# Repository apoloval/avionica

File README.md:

## Introduction

Avionica is a electronics platform used to build flight simulation systems.

## Status

Avionica is a work in progress. There is nothing usable yet.

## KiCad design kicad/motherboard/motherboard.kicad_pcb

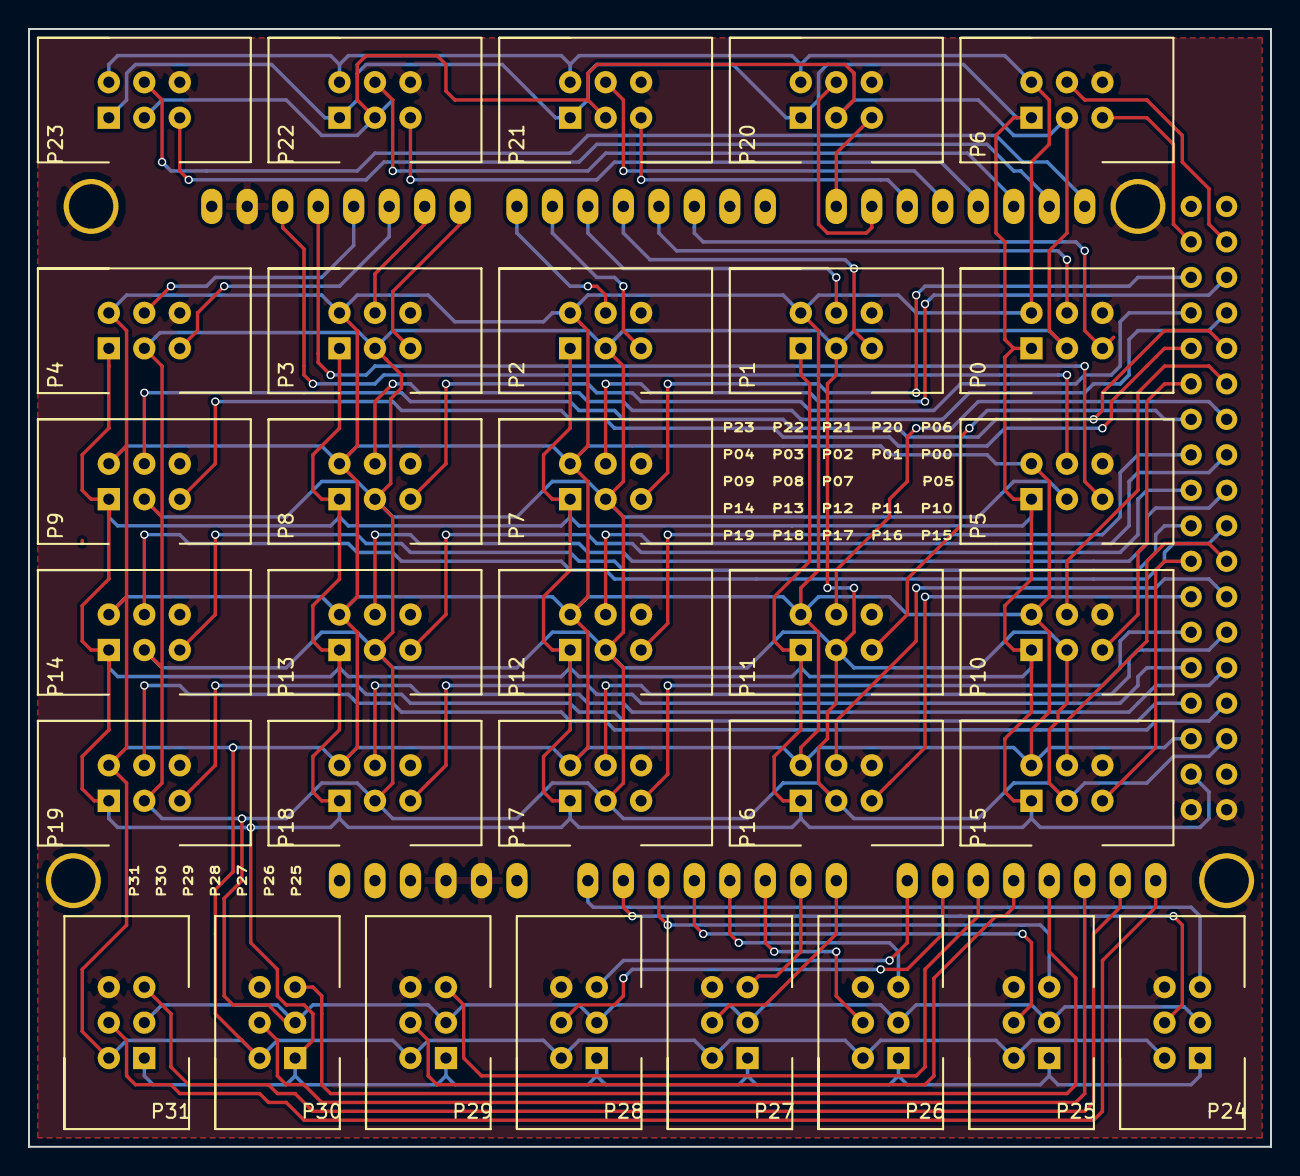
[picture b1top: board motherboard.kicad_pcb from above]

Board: 2 copper layers, 88.9 x 80.0 mm, 33 parts (0 on the bottom side), 68 nets.

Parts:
P0, P1, P2, P3, P4, P5, P6, P7, P8, P9, P10, P11, P12, P13, P14, P15, P16, P17, P18, P19, P20, P21, P22, P23, P24, P25, P26, P27, P28, P29, P30, P31: CONN06; idc-6p
SHIELD1: Arduino_Mega_Shield; arduino-mega-shield

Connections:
GND: P0.6, P1.6, P2.6, P3.6, P4.6, P5.6, P6.6, P7.6, P8.6, P9.6, P10.6, P11.6, P12.6, P13.6, P14.6, P15.6, P16.6, P17.6, P18.6, P19.6, P20.6, P21.6, P22.6, P23.6, P24.6, P25.6, P26.6, P27.6, P28.6, P29.6, P30.6, P31.6, SHIELD1.GND1, SHIELD1.GND2, SHIELD1.GND3, SHIELD1.GND4, SHIELD1.GND5
MISO: P0.2, P1.2, P2.2, P3.2, P4.2, P5.2, P6.2, P7.2, P8.2, P9.2, P10.2, P11.2, P12.2, P13.2, P14.2, P15.2, P16.2, P17.2, P18.2, P19.2, P20.2, P21.2, P22.2, P23.2, P24.2, P25.2, P26.2, P27.2, P28.2, P29.2, P30.2, P31.2, SHIELD1.50
MOSI: P0.3, P1.3, P2.3, P3.3, P4.3, P5.3, P6.3, P7.3, P8.3, P9.3, P10.3, P11.3, P12.3, P13.3, P14.3, P15.3, P16.3, P17.3, P18.3, P19.3, P20.3, P21.3, P22.3, P23.3, P24.3, P25.3, P26.3, P27.3, P28.3, P29.3, P30.3, P31.3, SHIELD1.51
P0.DAV: P0.5, SHIELD1.2
P0.SS: P0.4, SHIELD1.3
P1.DAV: P1.5, SHIELD1.4
P1.SS: P1.4, SHIELD1.5
P2.DAV: P2.5, SHIELD1.6
P2.SS: P2.4, SHIELD1.7
P3.DAV: P3.5, SHIELD1.8
P3.SS: P3.4, SHIELD1.9
P4.DAV: P4.5, SHIELD1.10
P4.SS: P4.4, SHIELD1.11
P5.DAV: P5.5, SHIELD1.12
P5.SS: P5.4, SHIELD1.13
P6.DAV: P6.5, SHIELD1.22
P6.SS: P6.4, SHIELD1.23
P7.DAV: P7.5, SHIELD1.24
P7.SS: P7.4, SHIELD1.25
P8.DAV: P8.5, SHIELD1.26
P8.SS: P8.4, SHIELD1.27
P9.DAV: P9.5, SHIELD1.28
P9.SS: P9.4, SHIELD1.29
P10.DAV: P10.5, SHIELD1.30
P10.SS: P10.4, SHIELD1.31
P11.DAV: P11.5, SHIELD1.32
P11.SS: P11.4, SHIELD1.33
P12.DAV: P12.5, SHIELD1.34
P12.SS: P12.4, SHIELD1.35
P13.DAV: P13.5, SHIELD1.36
P13.SS: P13.4, SHIELD1.37
P14.DAV: P14.5, SHIELD1.38
P14.SS: P14.4, SHIELD1.39
P15.DAV: P15.5, SHIELD1.40
P15.SS: P15.4, SHIELD1.41
P16.DAV: P16.5, SHIELD1.42
P16.SS: P16.4, SHIELD1.43
P17.DAV: P17.5, SHIELD1.44
P17.SS: P17.4, SHIELD1.45
P18.DAV: P18.5, SHIELD1.46
P18.SS: P18.4, SHIELD1.47
P19.DAV: P19.5, SHIELD1.48
P19.SS: P19.4, SHIELD1.49
P20.DAV: P20.5, SHIELD1.14
P20.SS: P20.4, SHIELD1.15
P21.DAV: P21.5, SHIELD1.16
P21.SS: P21.4, SHIELD1.17
P22.DAV: P22.5, SHIELD1.18
P22.SS: P22.4, SHIELD1.19
P23.DAV: P23.5, SHIELD1.20
P23.SS: P23.4, SHIELD1.21
P24.DAV: P24.5, SHIELD1.AD0
P24.SS: P24.4, SHIELD1.AD1
P25.DAV: P25.5, SHIELD1.AD2
P25.SS: P25.4, SHIELD1.AD3
P26.DAV: P26.5, SHIELD1.AD4
P26.SS: P26.4, SHIELD1.AD5
P27.DAV: P27.5, SHIELD1.AD6
P27.SS: P27.4, SHIELD1.AD7
P28.DAV: P28.5, SHIELD1.AD8
P28.SS: P28.4, SHIELD1.AD9
P29.DAV: P29.5, SHIELD1.AD10
P29.SS: P29.4, SHIELD1.AD11
P30.DAV: P30.5, SHIELD1.AD12
P30.SS: P30.4, SHIELD1.AD13
P31.DAV: P31.5, SHIELD1.AD14
P31.SS: P31.4, SHIELD1.AD15
SCK: P0.1, P1.1, P2.1, P3.1, P4.1, P5.1, P6.1, P7.1, P8.1, P9.1, P10.1, P11.1, P12.1, P13.1, P14.1, P15.1, P16.1, P17.1, P18.1, P19.1, P20.1, P21.1, P22.1, P23.1, P24.1, P25.1, P26.1, P27.1, P28.1, P29.1, P30.1, P31.1, SHIELD1.52

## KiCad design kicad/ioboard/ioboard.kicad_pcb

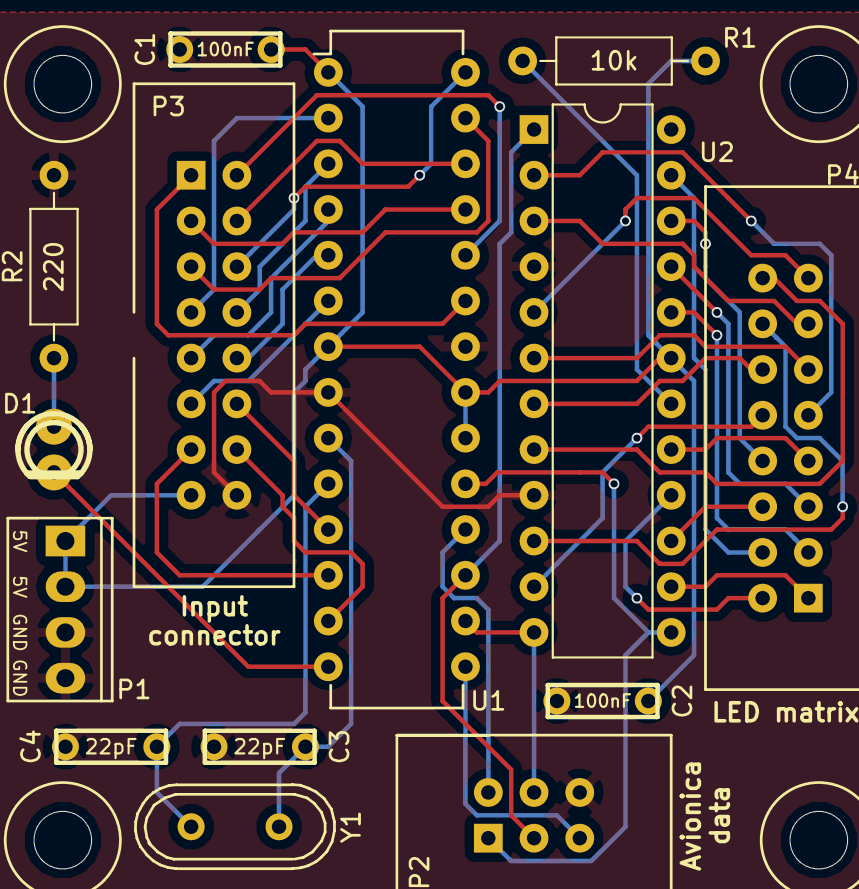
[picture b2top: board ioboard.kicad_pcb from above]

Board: 2 copper layers, 14 parts (0 on the bottom side), 42 nets.

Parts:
C1, C2: 100nF; Disc_capacitor
C3, C4: 22pF; Disc_capacitor
D1: LED; LED-th
P1: CONN04; kf2510-4p
P2: CONN06; idc-6p
P3, P4: CONN16; idc-16p
R1: 10k; Axial_resistor
R2: 220; Axial_resistor
U1: atmega328; DIP-28
U2: MAX7219; DIP-24
Y1: Crystal

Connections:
GND: C1.2, C2.2, C3.2, C4.2, P1.3, P1.4, P2.6, P3.16, R2.2, U1.8, U1.22, U2.4, U2.9
unnamed: C3.1, U1.9, Y1.1
unnamed: C4.1, U1.10, Y1.2
unnamed: D1.1, R2.1
unnamed: D1.2, U1.14
unnamed: P2.1, U1.19, U2.13
unnamed: P2.2, U1.18
unnamed: P2.3, U1.17, U2.1
unnamed: P2.4, U1.16, U2.12
unnamed: P2.5, U1.15
unnamed: P3.1, U1.23
unnamed: P3.2, U1.24
unnamed: P3.3, U1.25
unnamed: P3.4, U1.26
unnamed: P3.5, U1.27
unnamed: P3.6, U1.28
unnamed: P3.7, U1.2
unnamed: P3.8, U1.3
unnamed: P3.9, U1.4
unnamed: P3.10, U1.5
unnamed: P3.11, U1.6
unnamed: P3.12, U1.11
unnamed: P3.13, U1.12
unnamed: P3.14, U1.13
unnamed: P4.1, U2.14
unnamed: P4.2, U2.16
unnamed: P4.3, U2.20
unnamed: P4.4, U2.23
unnamed: P4.5, U2.21
unnamed: P4.6, U2.15
unnamed: P4.7, U2.17
unnamed: P4.8, U2.22
unnamed: P4.9, U2.2
unnamed: P4.10, U2.11
unnamed: P4.11, U2.6
unnamed: P4.12, U2.7
unnamed: P4.13, U2.3
unnamed: P4.14, U2.10
unnamed: P4.15, U2.5
unnamed: P4.16, U2.8
unnamed: R1.2, U2.18
VCC: C1.1, C2.1, P1.1, P1.2, P3.15, R1.1, U1.1, U1.7, U1.20, U1.21, U2.19

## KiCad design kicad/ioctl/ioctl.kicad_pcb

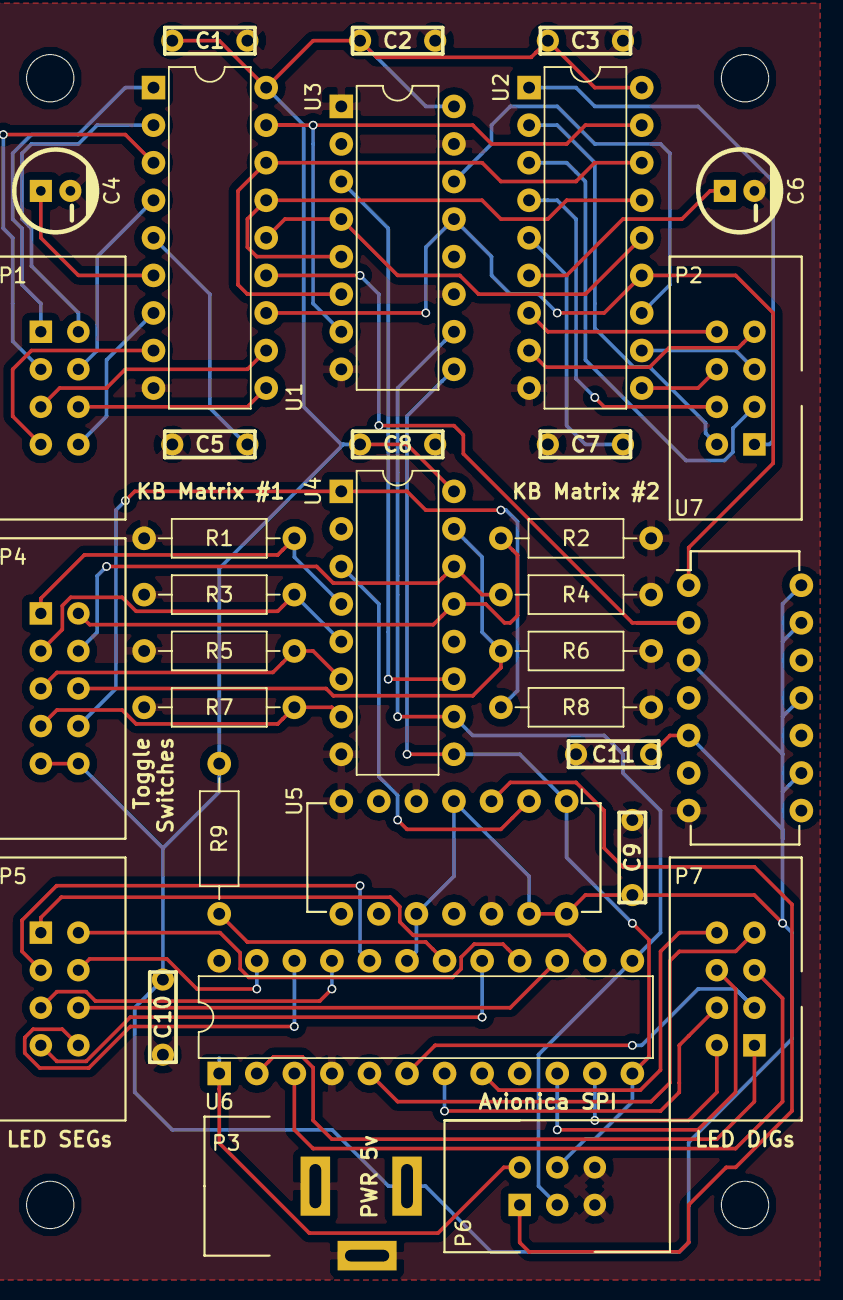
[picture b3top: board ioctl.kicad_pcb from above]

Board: 2 copper layers, 34 parts (0 on the bottom side), 60 nets.

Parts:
C1, C2, C3, C5, C7, C8, C9, C10, C11: 100nF; Disc_capacitor
C4, C6: 1uF; Radial_capacitor
P1, P2, P5, P7: CONN_01X08; idc-8p
P3: CONN_01X03; Jack_55_21
P4: CONN_02X05; idc-10p
P6: CONN_02X03; idc-6p
R1, R2, R3, R4, R5, R6, R7, R8: 10K; Axial_resistor
R9: 10k; Axial_resistor
U1, U2: 74922; DIP-18
U3, U4: CD4021; DIP-16
U5: 74125; DIP-14
U6: MAX7219; DIP-24
U7: 7404; DIP-14

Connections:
GND: C1.2, C2.2, C3.2, C4.2, C5.1, C6.2, C7.1, C8.2, C9.2, C10.2, C11.2, P3.2, P3.3, P6.5, P6.6, R1.2, R2.2, R3.2, R4.2, R5.2, R6.2, R7.2, R8.2, U1.9, U2.9, U3.1, U3.8, U3.11, U3.15, U4.8, U5.5, U5.7, U5.9, U5.12, U6.4, U6.9, U7.7
MISO: P6.1, U5.3
MOSI: P6.2, U6.1
unnamed: C4.1, U1.6
unnamed: C5.2, U1.5
unnamed: C6.1, U2.6
unnamed: C7.2, U2.5
unnamed: P1.1, U1.1
unnamed: P1.2, U1.2
unnamed: P1.3, U1.3
unnamed: P1.4, U1.4
unnamed: P1.5, U1.11
unnamed: P1.6, U1.10
unnamed: P1.7, U1.8
unnamed: P1.8, U1.7
unnamed: P2.1, U2.1
unnamed: P2.2, U2.2
unnamed: P2.3, U2.3
unnamed: P2.4, U2.4
unnamed: P2.5, U2.11
unnamed: P2.6, U2.10
unnamed: P2.7, U2.8
unnamed: P2.8, U2.7
unnamed: P4.1, R1.1, U4.4
unnamed: P4.2, R2.1, U4.13
unnamed: P4.3, R3.1, U4.5
unnamed: P4.4, R4.1, U4.14
unnamed: P4.5, R5.1, U4.6
unnamed: P4.6, R6.1, U4.15
unnamed: P4.7, R7.1, U4.7
unnamed: P4.8, R8.1, U4.1
unnamed: P5.1, U6.14
unnamed: P5.2, U6.16
unnamed: P5.3, U6.20
unnamed: P5.4, U6.23
unnamed: P5.5, U6.21
unnamed: P5.6, U6.15
unnamed: P5.7, U6.17
unnamed: P5.8, U6.22
unnamed: P7.1, U6.2
unnamed: P7.2, U6.11
unnamed: P7.3, U6.6
unnamed: P7.4, U6.7
unnamed: P7.5, U6.3
unnamed: P7.6, U6.10
unnamed: P7.7, U6.5
unnamed: P7.8, U6.8
unnamed: R9.2, U6.18
unnamed: U1.12, U2.13, U3.13, U7.1
unnamed: U1.13, U7.2
unnamed: U1.14, U2.14, U3.4
unnamed: U1.15, U2.15, U3.5
unnamed: U1.16, U2.16, U3.6
unnamed: U1.17, U2.17, U3.7
unnamed: U2.12, U3.14
unnamed: U3.3, U4.11
unnamed: U4.3, U5.2
SCK: P6.3, U3.10, U4.10, U6.13
VCC: C1.1, C2.1, C3.1, C8.1, C9.1, C10.1, C11.1, P3.1, P4.9, P4.10, R9.1, U1.18, U2.18, U3.16, U4.16, U5.4, U5.10, U5.13, U5.14, U6.19, U7.3, U7.5, U7.9, U7.11, U7.13, U7.14
~SS: P6.4, U3.9, U4.9, U5.1, U6.12

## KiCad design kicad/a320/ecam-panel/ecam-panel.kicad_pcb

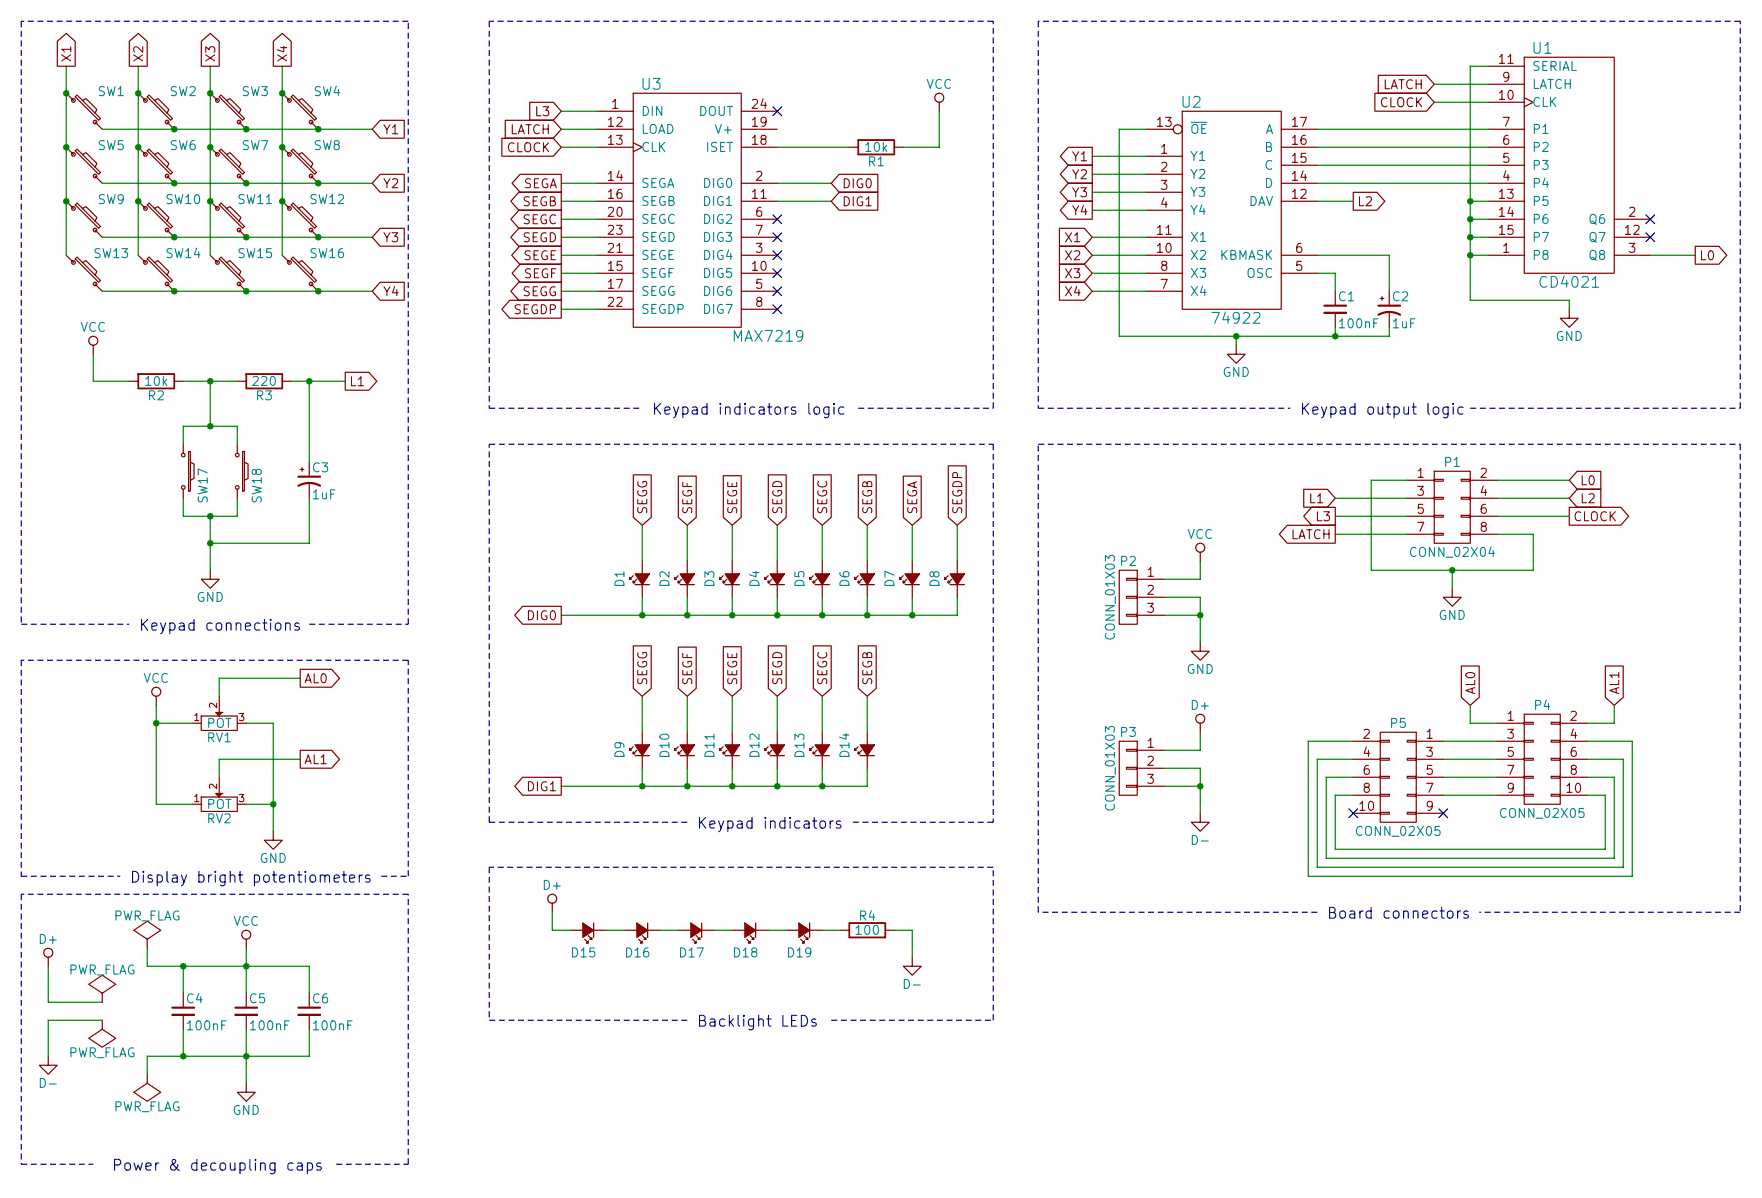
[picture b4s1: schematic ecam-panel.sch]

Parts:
C1, C4, C5, C6: 100nF; Disc_capacitor
C2, C3: 1uF; Radial_capacitor
D1, D2, D3, D4, D5, D6, D7, D8, D9, D10, D11, D12, D13, D14: Led_Small; Pin_Header_1x02
D15, D16, D17, D18, D19: Led_Small; LED-1210
P1: CONN_02X04; idc-8p
P2, P3: CONN_01X03; Jack_55_21
P4, P5: CONN_02X05; idc-10p
R1, R2: 10k; Axial_resistor
R3: 220; Axial_resistor
R4: 100; Axial_resistor
RV1, RV2: POT; Pin_Header_1x03
SW1, SW2, SW3, SW4, SW5, SW6, SW7, SW8, SW9, SW10, SW11, SW12, SW13, SW14, SW15, SW16: SW_PUSH_SMALL; Omron-B3F-12mm
SW17, SW18: SW_PUSH_SMALL_H; Omron-B3F-12mm
U1: CD4021; DIP-16
U2: 74922; DIP-18
U3: MAX7219; DIP-24

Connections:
AL0: P4.1, RV1.2
AL1: P4.2, RV2.2
CLOCK: P1.6, U1.10 (CLK), U3.13 (CLK)
D+: D15.2 (A), P3.1
D-: P3.2, P3.3, R4.2
DIG0: D1.1 (K), D2.1 (K), D3.1 (K), D4.1 (K), D5.1 (K), D6.1 (K), D7.1 (K), D8.1 (K), U3.2 (DIG0)
DIG1: D9.1 (K), D10.1 (K), D11.1 (K), D12.1 (K), D13.1 (K), D14.1 (K), U3.11 (DIG1)
GND: C1.2, C2.2, C3.2, C4.2, C5.2, C6.2, P1.1, P1.8, P2.2, P2.3, RV1.3, RV2.3, SW17.2, SW18.2, U1.1 (P8), U1.8 (GND), U1.11 (SERIAL), U1.13 (P5), U1.14 (P6), U1.15 (P7), U2.9 (GND), U2.13 (~OE), U3.4 (GND), U3.9 (GND)
L0: P1.2, U1.3 (Q8)
L1: C3.1, P1.3, R3.1
L2: P1.4, U2.12 (DAV)
L3: P1.5, U3.1 (DIN)
LATCH: P1.7, U1.9 (LATCH), U3.12 (LOAD)
unnamed: C1.1, U2.5 (OSC)
unnamed: C2.1, U2.6 (KBMASK)
unnamed: D15.1 (K), D16.2 (A)
unnamed: D16.1 (K), D17.2 (A)
unnamed: D17.1 (K), D18.2 (A)
unnamed: D18.1 (K), D19.2 (A)
unnamed: D19.1 (K), R4.1
unnamed: P4.3, P5.1
unnamed: P4.4, P5.2
unnamed: P4.5, P5.3
unnamed: P4.6, P5.4
unnamed: P4.7, P5.5
unnamed: P4.8, P5.6
unnamed: P4.9, P5.7
unnamed: P4.10, P5.8
unnamed: R1.2, U3.18 (ISET)
unnamed: R2.1, R3.2, SW17.1, SW18.1
unnamed: U1.4, U2.14 (D)
unnamed: U1.5 (P3), U2.15 (C)
unnamed: U1.6 (P2), U2.16 (B)
unnamed: U1.7 (P1), U2.17 (A)
SEGA: D7.2 (A), U3.14 (SEGA)
SEGB: D6.2 (A), D14.2 (A), U3.16 (SEGB)
SEGC: D5.2 (A), D13.2 (A), U3.20 (SEGC)
SEGD: D4.2 (A), D12.2 (A), U3.23 (SEGD)
SEGDP: D8.2 (A), U3.22 (SEGDP)
SEGE: D3.2 (A), D11.2 (A), U3.21 (SEGE)
SEGF: D2.2 (A), D10.2 (A), U3.15 (SEGF)
SEGG: D1.2 (A), D9.2 (A), U3.17 (SEGG)
VCC: C4.1, C5.1, C6.1, P2.1, R1.1, R2.2, RV1.1, RV2.1, U1.16 (VCC), U2.18 (VCC), U3.19 (V+)
X1: SW1.1, SW5.1, SW9.1, SW13.1, U2.11 (X1)
X2: SW2.1, SW6.1, SW10.1, SW14.1, U2.10 (X2)
X3: SW3.1, SW7.1, SW11.1, SW15.1, U2.8 (X3)
X4: SW4.1, SW8.1, SW12.1, SW16.1, U2.7 (X4)
Y1: SW1.2, SW2.2, SW3.2, SW4.2, U2.1 (Y1)
Y2: SW5.2, SW6.2, SW7.2, SW8.2, U2.2 (Y2)
Y3: SW9.2, SW10.2, SW11.2, SW12.2, U2.3 (Y3)
Y4: SW13.2, SW14.2, SW15.2, SW16.2, U2.4 (Y4)

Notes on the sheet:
Keypad indicators
Board connectors
Power & decoupling caps
Display bright potentiometers
Keypad connections
Keypad indicators logic
Keypad output logic
Backlight LEDs

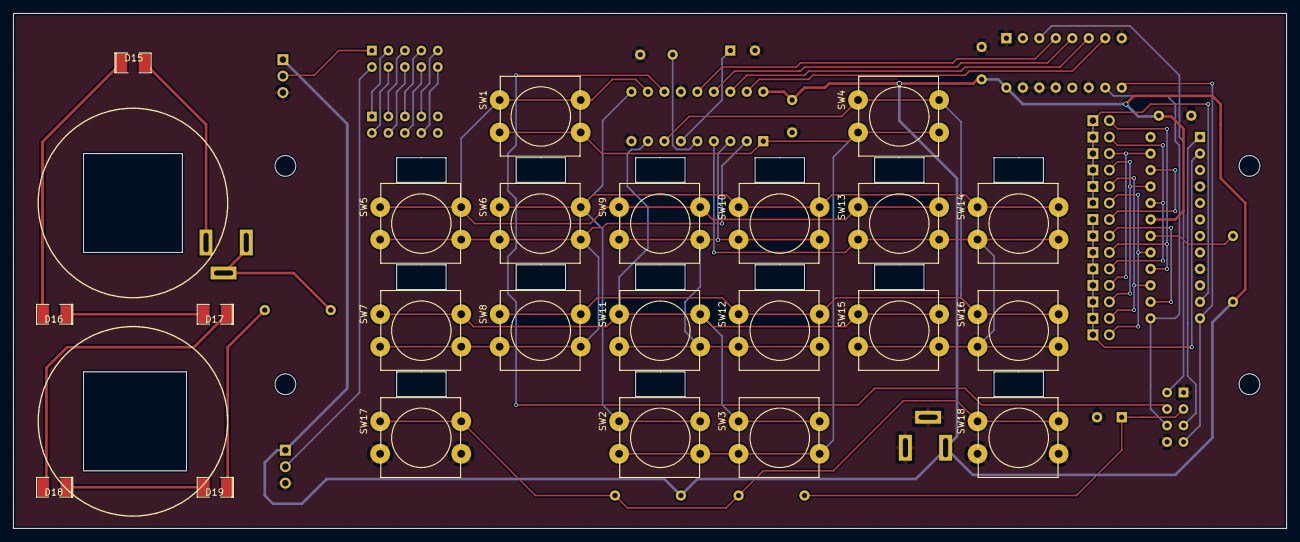
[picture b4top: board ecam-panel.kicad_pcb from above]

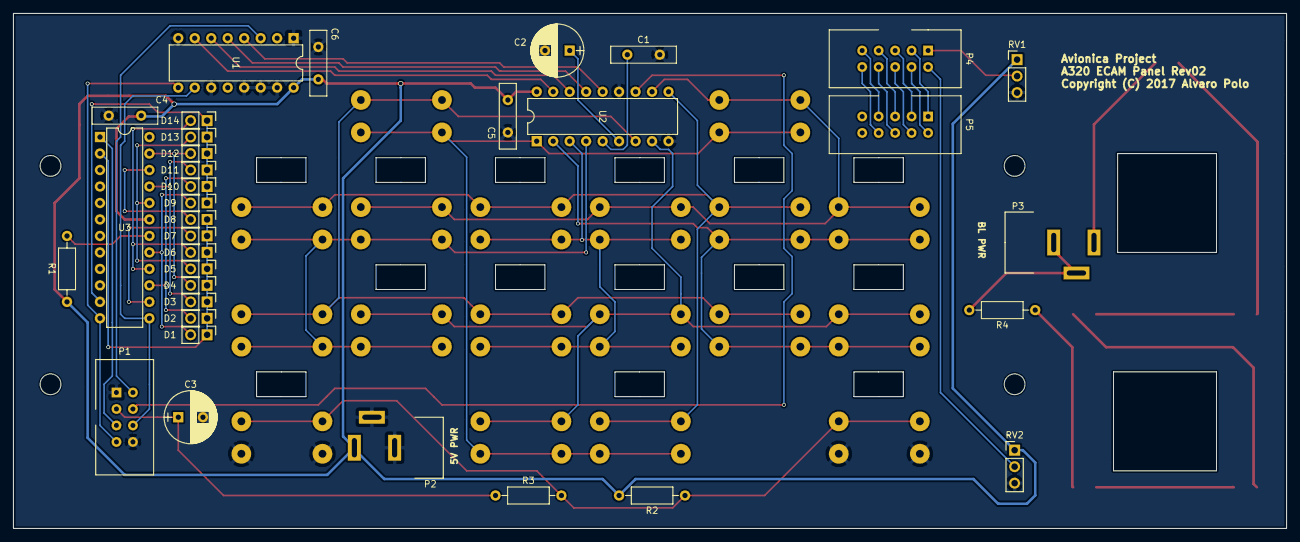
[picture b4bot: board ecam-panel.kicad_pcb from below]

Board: 2 copper layers, 196.2 x 79.4 mm, 57 parts (34 on the bottom side), 51 nets.

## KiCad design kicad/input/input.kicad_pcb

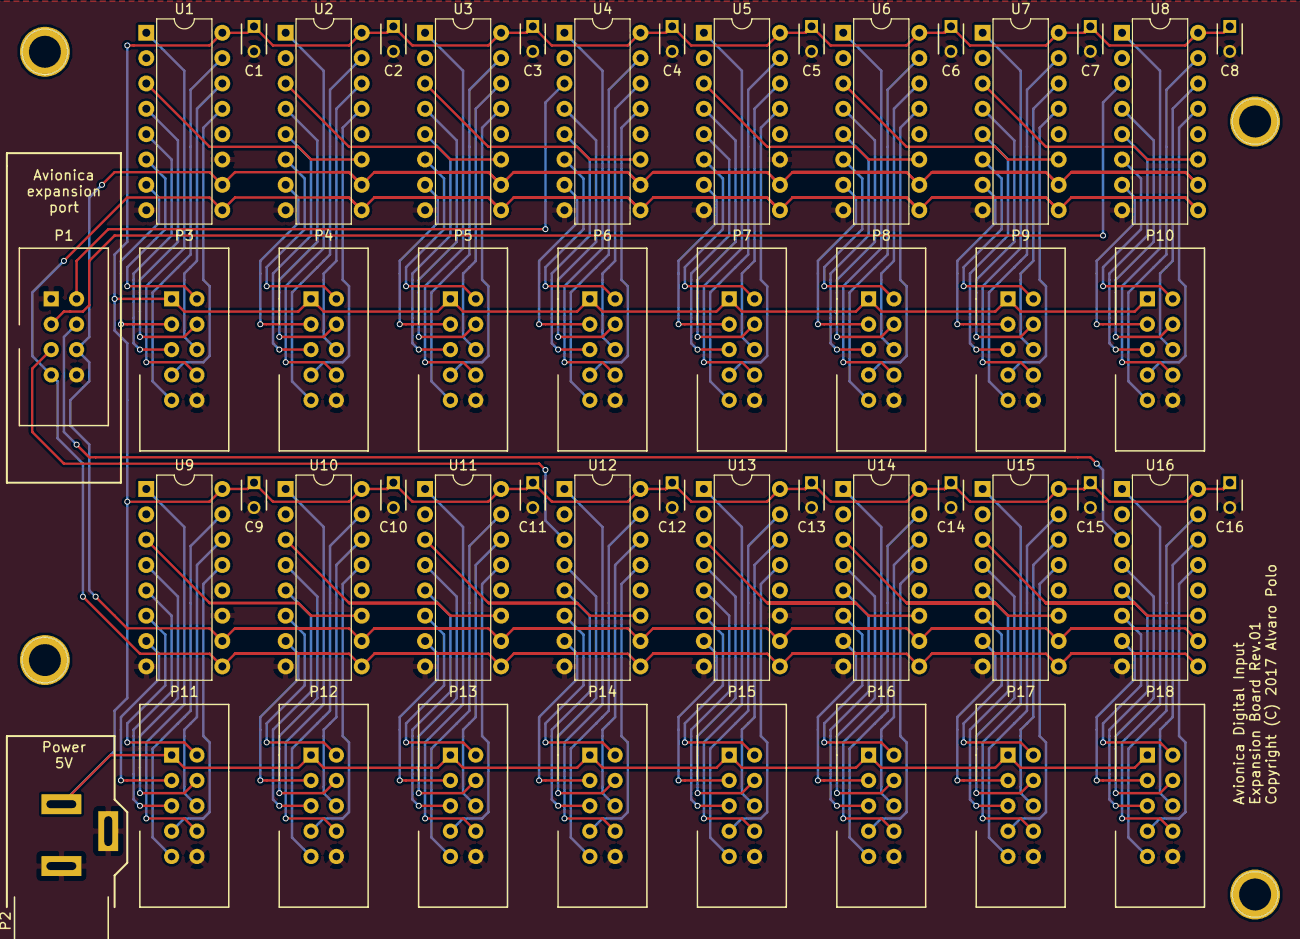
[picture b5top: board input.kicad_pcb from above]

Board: 2 copper layers, 50 parts (0 on the bottom side), 148 nets.

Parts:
C1, C2, C3, C4, C5, C6, C7, C8, C9, C10, C11, C12, C13, C14, C15, C16: C_Small; C_Disc_D3_P2.5
P1: CONN_02X04; idc-8p
P2: CONN_01X03; Jack_55_21
P3, P4, P5, P6, P7, P8, P9, P10, P11, P12, P13, P14, P15, P16, P17, P18: CONN_02X05; idc-10p
U1, U2, U3, U4, U5, U6, U7, U8, U9, U10, U11, U12, U13, U14, U15, U16: CD4021; DIP-16_W7.62mm

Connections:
/CLOCK: P1.6, U1.10, U2.10, U3.10, U4.10, U5.10, U6.10, U7.10, U8.10, U9.10, U10.10, U11.10, U12.10, U13.10, U14.10, U15.10, U16.10
/DATA.A: P1.2, U4.3
/DATA.B: P1.3, U8.3
/DATA.C: P1.4, U16.3
/DATA.D: P1.5, U12.3
/LATCH: P1.7, U1.9, U2.9, U3.9, U4.9, U5.9, U6.9, U7.9, U8.9, U9.9, U10.9, U11.9, U12.9, U13.9, U14.9, U15.9, U16.9
/LINE-A/DATA1.1: P3.3, U1.7
/LINE-A/DATA1.2: P3.2, U1.6
/LINE-A/DATA1.3: P3.5, U1.5
/LINE-A/DATA1.4: P3.4, U1.4
/LINE-A/DATA1.5: P3.7, U1.13
/LINE-A/DATA1.6: P3.6, U1.14
/LINE-A/DATA1.7: P3.9, U1.15
/LINE-A/DATA1.8: P3.8, U1.1
/LINE-A/DATA2.1: P4.3, U2.7
/LINE-A/DATA2.2: P4.2, U2.6
/LINE-A/DATA2.3: P4.5, U2.5
/LINE-A/DATA2.4: P4.4, U2.4
/LINE-A/DATA2.5: P4.7, U2.13
/LINE-A/DATA2.6: P4.6, U2.14
/LINE-A/DATA2.7: P4.9, U2.15
/LINE-A/DATA2.8: P4.8, U2.1
/LINE-A/DATA3.1: P5.3, U3.7
/LINE-A/DATA3.2: P5.2, U3.6
/LINE-A/DATA3.3: P5.5, U3.5
/LINE-A/DATA3.4: P5.4, U3.4
/LINE-A/DATA3.5: P5.7, U3.13
/LINE-A/DATA3.6: P5.6, U3.14
/LINE-A/DATA3.7: P5.9, U3.15
/LINE-A/DATA3.8: P5.8, U3.1
/LINE-A/DATA4.1: P6.3, U4.7
/LINE-A/DATA4.2: P6.2, U4.6
/LINE-A/DATA4.3: P6.5, U4.5
/LINE-A/DATA4.4: P6.4, U4.4
/LINE-A/DATA4.5: P6.7, U4.13
/LINE-A/DATA4.6: P6.6, U4.14
/LINE-A/DATA4.7: P6.9, U4.15
/LINE-A/DATA4.8: P6.8, U4.1
/LINE-B/DATA1.1: P7.3, U5.7
/LINE-B/DATA1.2: P7.2, U5.6
/LINE-B/DATA1.3: P7.5, U5.5
/LINE-B/DATA1.4: P7.4, U5.4
/LINE-B/DATA1.5: P7.7, U5.13
/LINE-B/DATA1.6: P7.6, U5.14
/LINE-B/DATA1.7: P7.9, U5.15
/LINE-B/DATA1.8: P7.8, U5.1
/LINE-B/DATA2.1: P8.3, U6.7
/LINE-B/DATA2.2: P8.2, U6.6
/LINE-B/DATA2.3: P8.5, U6.5
/LINE-B/DATA2.4: P8.4, U6.4
/LINE-B/DATA2.5: P8.7, U6.13
/LINE-B/DATA2.6: P8.6, U6.14
/LINE-B/DATA2.7: P8.9, U6.15
/LINE-B/DATA2.8: P8.8, U6.1
/LINE-B/DATA3.1: P9.3, U7.7
/LINE-B/DATA3.2: P9.2, U7.6
/LINE-B/DATA3.3: P9.5, U7.5
/LINE-B/DATA3.4: P9.4, U7.4
/LINE-B/DATA3.5: P9.7, U7.13
/LINE-B/DATA3.6: P9.6, U7.14
/LINE-B/DATA3.7: P9.9, U7.15
/LINE-B/DATA3.8: P9.8, U7.1
/LINE-B/DATA4.1: P10.3, U8.7
/LINE-B/DATA4.2: P10.2, U8.6
/LINE-B/DATA4.3: P10.5, U8.5
/LINE-B/DATA4.4: P10.4, U8.4
/LINE-B/DATA4.5: P10.7, U8.13
/LINE-B/DATA4.6: P10.6, U8.14
/LINE-B/DATA4.7: P10.9, U8.15
/LINE-B/DATA4.8: P10.8, U8.1
/LINE-C/DATA1.1: P15.3, U13.7
/LINE-C/DATA1.2: P15.2, U13.6
/LINE-C/DATA1.3: P15.5, U13.5
/LINE-C/DATA1.4: P15.4, U13.4
/LINE-C/DATA1.5: P15.7, U13.13
/LINE-C/DATA1.6: P15.6, U13.14
/LINE-C/DATA1.7: P15.9, U13.15
/LINE-C/DATA1.8: P15.8, U13.1
/LINE-C/DATA2.1: P16.3, U14.7
/LINE-C/DATA2.2: P16.2, U14.6
/LINE-C/DATA2.3: P16.5, U14.5
/LINE-C/DATA2.4: P16.4, U14.4
/LINE-C/DATA2.5: P16.7, U14.13
/LINE-C/DATA2.6: P16.6, U14.14
/LINE-C/DATA2.7: P16.9, U14.15
/LINE-C/DATA2.8: P16.8, U14.1
/LINE-C/DATA3.1: P17.3, U15.7
/LINE-C/DATA3.2: P17.2, U15.6
/LINE-C/DATA3.3: P17.5, U15.5
/LINE-C/DATA3.4: P17.4, U15.4
/LINE-C/DATA3.5: P17.7, U15.13
/LINE-C/DATA3.6: P17.6, U15.14
/LINE-C/DATA3.7: P17.9, U15.15
/LINE-C/DATA3.8: P17.8, U15.1
/LINE-C/DATA4.1: P18.3, U16.7
/LINE-C/DATA4.2: P18.2, U16.6
/LINE-C/DATA4.3: P18.5, U16.5
/LINE-C/DATA4.4: P18.4, U16.4
/LINE-C/DATA4.5: P18.7, U16.13
/LINE-C/DATA4.6: P18.6, U16.14
/LINE-C/DATA4.7: P18.9, U16.15
/LINE-C/DATA4.8: P18.8, U16.1
/LINE-D/DATA1.1: P11.3, U9.7
/LINE-D/DATA1.2: P11.2, U9.6
/LINE-D/DATA1.3: P11.5, U9.5
/LINE-D/DATA1.4: P11.4, U9.4
/LINE-D/DATA1.5: P11.7, U9.13
/LINE-D/DATA1.6: P11.6, U9.14
/LINE-D/DATA1.7: P11.9, U9.15
/LINE-D/DATA1.8: P11.8, U9.1
/LINE-D/DATA2.1: P12.3, U10.7
/LINE-D/DATA2.2: P12.2, U10.6
/LINE-D/DATA2.3: P12.5, U10.5
/LINE-D/DATA2.4: P12.4, U10.4
/LINE-D/DATA2.5: P12.7, U10.13
/LINE-D/DATA2.6: P12.6, U10.14
/LINE-D/DATA2.7: P12.9, U10.15
/LINE-D/DATA2.8: P12.8, U10.1
/LINE-D/DATA3.1: P13.3, U11.7
/LINE-D/DATA3.2: P13.2, U11.6
/LINE-D/DATA3.3: P13.5, U11.5
/LINE-D/DATA3.4: P13.4, U11.4
/LINE-D/DATA3.5: P13.7, U11.13
/LINE-D/DATA3.6: P13.6, U11.14
/LINE-D/DATA3.7: P13.9, U11.15
/LINE-D/DATA3.8: P13.8, U11.1
/LINE-D/DATA4.1: P14.3, U12.7
/LINE-D/DATA4.2: P14.2, U12.6
/LINE-D/DATA4.3: P14.5, U12.5
/LINE-D/DATA4.4: P14.4, U12.4
/LINE-D/DATA4.5: P14.7, U12.13
/LINE-D/DATA4.6: P14.6, U12.14
/LINE-D/DATA4.7: P14.9, U12.15
/LINE-D/DATA4.8: P14.8, U12.1
GND: C1.2, C2.2, C3.2, C4.2, C5.2, C6.2, C7.2, C8.2, C9.2, C10.2, C11.2, C12.2, C13.2, C14.2, C15.2, C16.2, P1.1, P1.8, P2.2, P2.3, P3.10, P4.10, P5.10, P6.10, P7.10, P8.10, P9.10, P10.10, P11.10, P12.10, P13.10, P14.10, P15.10, P16.10, P17.10, P18.10, U1.8, U1.11, U2.8, U3.8, U4.8, U5.8, U5.11, U6.8, U7.8, U8.8, U9.8, U9.11, U10.8, U11.8, U12.8, U13.8, U13.11, U14.8, U15.8, U16.8
unnamed: U1.3, U2.11
unnamed: U2.3, U3.11
unnamed: U3.3, U4.11
unnamed: U5.3, U6.11
unnamed: U6.3, U7.11
unnamed: U7.3, U8.11
unnamed: U10.3, U11.11
unnamed: U9.3, U10.11
unnamed: U11.3, U12.11
unnamed: U13.3, U14.11
unnamed: U14.3, U15.11
unnamed: U15.3, U16.11
VCC: C1.1, C2.1, C3.1, C4.1, C5.1, C6.1, C7.1, C8.1, C9.1, C10.1, C11.1, C12.1, C13.1, C14.1, C15.1, C16.1, P2.1, P3.1, P4.1, P5.1, P6.1, P7.1, P8.1, P9.1, P10.1, P11.1, P12.1, P13.1, P14.1, P15.1, P16.1, P17.1, P18.1, U1.16, U2.16, U3.16, U4.16, U5.16, U6.16, U7.16, U8.16, U9.16, U10.16, U11.16, U12.16, U13.16, U14.16, U15.16, U16.16

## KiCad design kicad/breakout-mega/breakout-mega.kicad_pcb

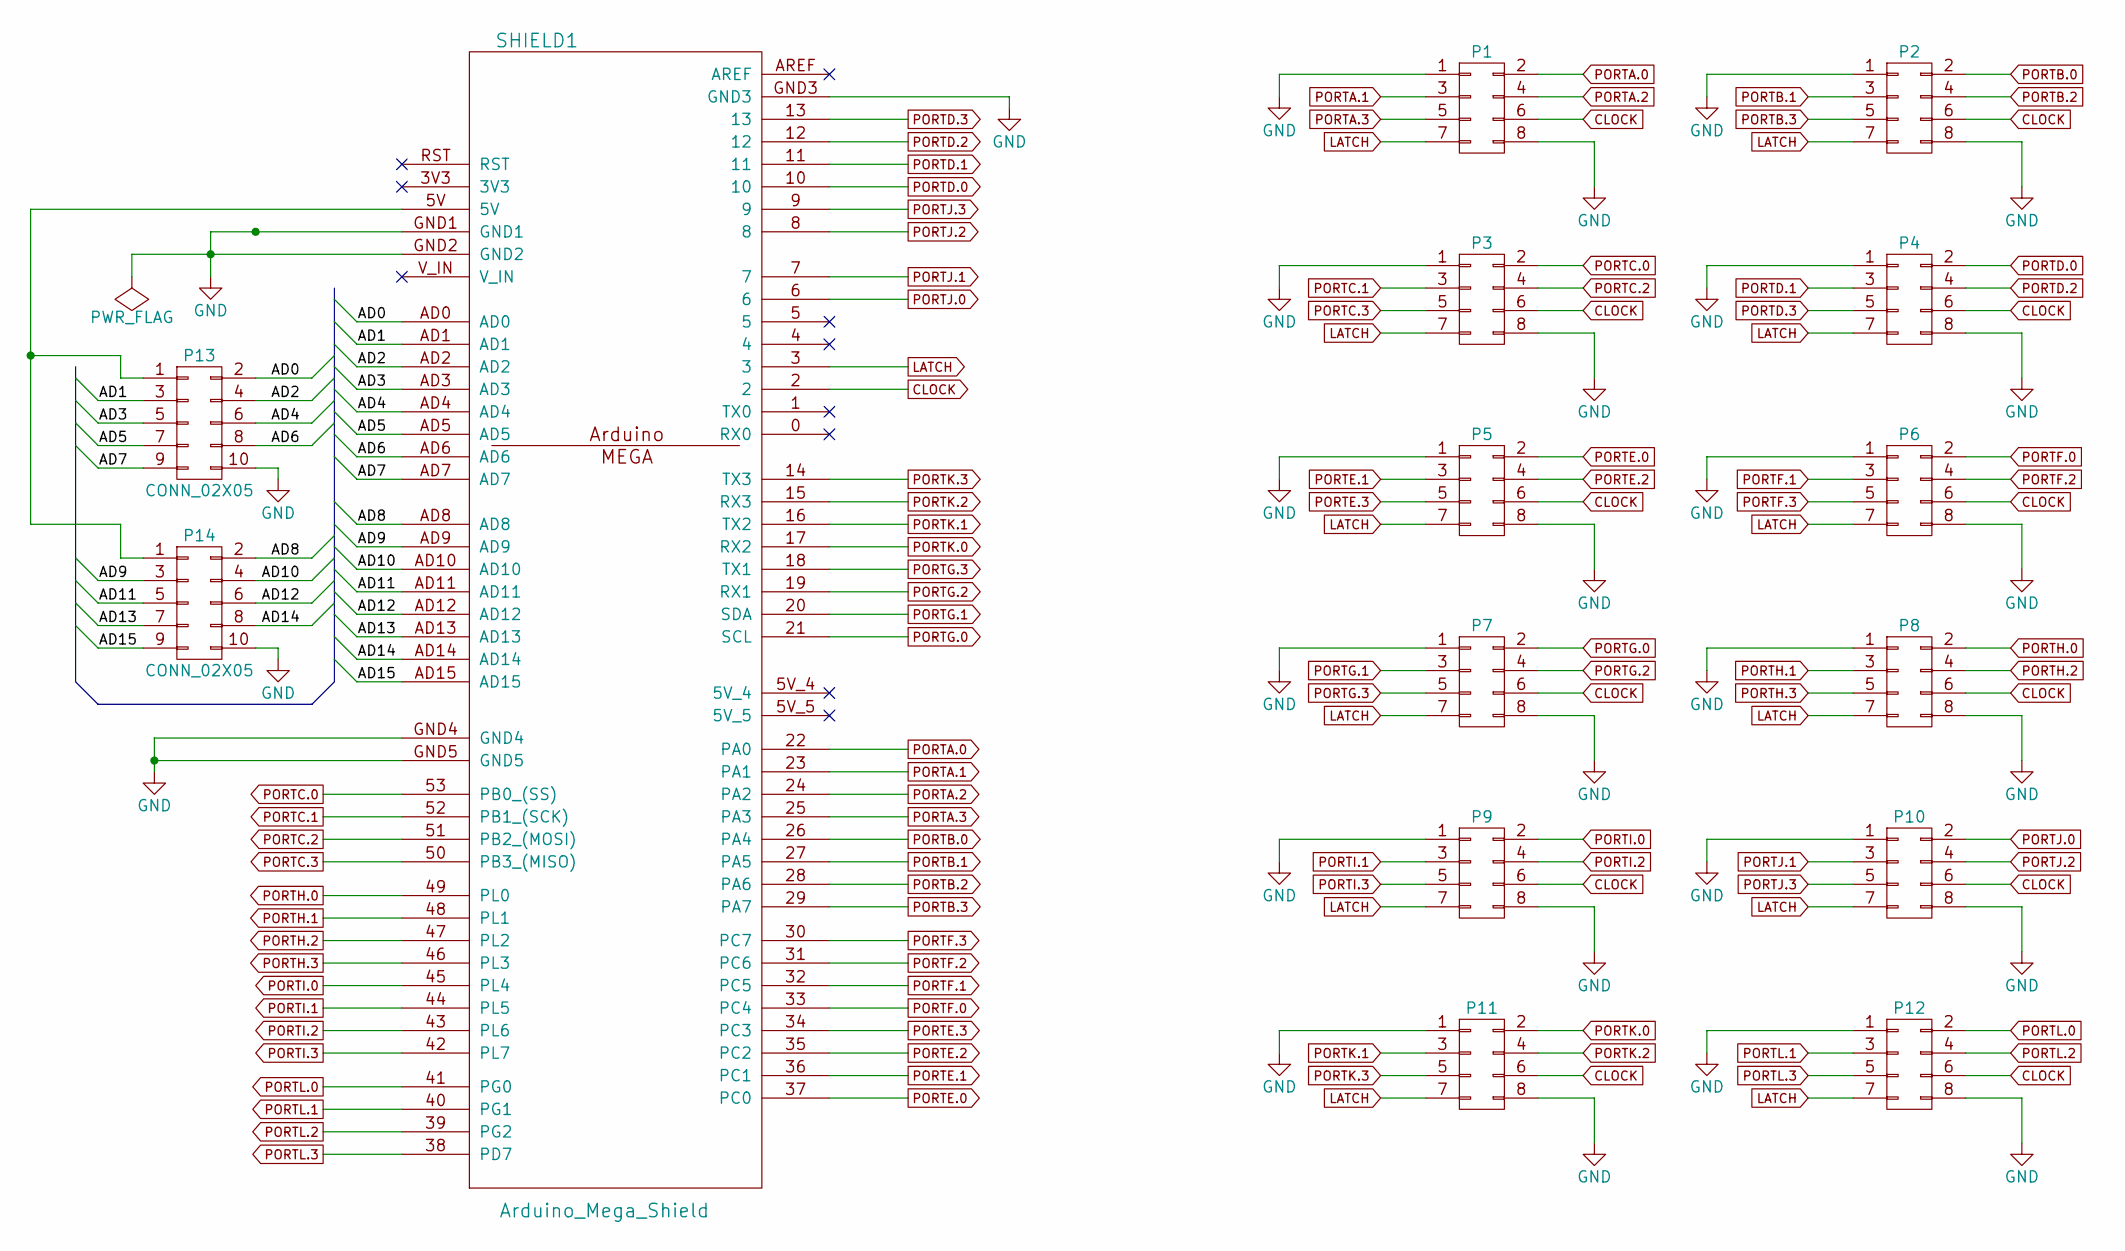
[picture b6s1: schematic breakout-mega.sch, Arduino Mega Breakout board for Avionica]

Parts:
P1, P2, P3, P4, P5, P6, P7, P8, P9, P10, P11, P12: CONN_02X04; idc-8p
P13, P14: CONN_02X05; idc-10p
SHIELD1: Arduino_Mega_Shield; arduino-mega-shield

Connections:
/AD0: P13.2, SHIELD1.AD0
/AD1: P13.3, SHIELD1.AD1
/AD2: P13.4, SHIELD1.AD2
/AD3: P13.5, SHIELD1.AD3
/AD4: P13.6, SHIELD1.AD4
/AD5: P13.7, SHIELD1.AD5
/AD6: P13.8, SHIELD1.AD6
/AD7: P13.9, SHIELD1.AD7
/AD8: P14.2, SHIELD1.AD8
/AD9: P14.3, SHIELD1.AD9
/AD10: P14.4, SHIELD1.AD10
/AD11: P14.5, SHIELD1.AD11
/AD12: P14.6, SHIELD1.AD12
/AD13: P14.7, SHIELD1.AD13
/AD14: P14.8, SHIELD1.AD14
/AD15: P14.9, SHIELD1.AD15
CLOCK: P1.6, P2.6, P3.6, P4.6, P5.6, P6.6, P7.6, P8.6, P9.6, P10.6, P11.6, P12.6, SHIELD1.2
GND: P1.1, P1.8, P2.1, P2.8, P3.1, P3.8, P4.1, P4.8, P5.1, P5.8, P6.1, P6.8, P7.1, P7.8, P8.1, P8.8, P9.1, P9.8, P10.1, P10.8, P11.1, P11.8, P12.1, P12.8, P13.10, P14.10, SHIELD1.GND1, SHIELD1.GND2, SHIELD1.GND3, SHIELD1.GND4, SHIELD1.GND5
LATCH: P1.7, P2.7, P3.7, P4.7, P5.7, P6.7, P7.7, P8.7, P9.7, P10.7, P11.7, P12.7, SHIELD1.3
unnamed: P13.1, P14.1, SHIELD1.5V
PORTA.0: P1.2, SHIELD1.22 (PA0)
PORTA.1: P1.3, SHIELD1.23 (PA1)
PORTA.2: P1.4, SHIELD1.24 (PA2)
PORTA.3: P1.5, SHIELD1.25 (PA3)
PORTB.0: P2.2, SHIELD1.26 (PA4)
PORTB.1: P2.3, SHIELD1.27 (PA5)
PORTB.2: P2.4, SHIELD1.28 (PA6)
PORTB.3: P2.5, SHIELD1.29 (PA7)
PORTC.0: P3.2, SHIELD1.53 (PB0_(SS))
PORTC.1: P3.3, SHIELD1.52 (PB1_(SCK))
PORTC.2: P3.4, SHIELD1.51 (PB2_(MOSI))
PORTC.3: P3.5, SHIELD1.50 (PB3_(MISO))
PORTD.0: P4.2, SHIELD1.10
PORTD.1: P4.3, SHIELD1.11
PORTD.2: P4.4, SHIELD1.12
PORTD.3: P4.5, SHIELD1.13
PORTE.0: P5.2, SHIELD1.37 (PC0)
PORTE.1: P5.3, SHIELD1.36 (PC1)
PORTE.2: P5.4, SHIELD1.35 (PC2)
PORTE.3: P5.5, SHIELD1.34 (PC3)
PORTF.0: P6.2, SHIELD1.33 (PC4)
PORTF.1: P6.3, SHIELD1.32 (PC5)
PORTF.2: P6.4, SHIELD1.31 (PC6)
PORTF.3: P6.5, SHIELD1.30 (PC7)
PORTG.0: P7.2, SHIELD1.21 (SCL)
PORTG.1: P7.3, SHIELD1.20 (SDA)
PORTG.2: P7.4, SHIELD1.19 (RX1)
PORTG.3: P7.5, SHIELD1.18 (TX1)
PORTH.0: P8.2, SHIELD1.49 (PL0)
PORTH.1: P8.3, SHIELD1.48 (PL1)
PORTH.2: P8.4, SHIELD1.47 (PL2)
PORTH.3: P8.5, SHIELD1.46 (PL3)
PORTI.0: P9.2, SHIELD1.45 (PL4)
PORTI.1: P9.3, SHIELD1.44 (PL5)
PORTI.2: P9.4, SHIELD1.43 (PL6)
PORTI.3: P9.5, SHIELD1.42 (PL7)
PORTJ.0: P10.2, SHIELD1.6
PORTJ.1: P10.3, SHIELD1.7
PORTJ.2: P10.4, SHIELD1.8
PORTJ.3: P10.5, SHIELD1.9
PORTK.0: P11.2, SHIELD1.17 (RX2)
PORTK.1: P11.3, SHIELD1.16 (TX2)
PORTK.2: P11.4, SHIELD1.15 (RX3)
PORTK.3: P11.5, SHIELD1.14 (TX3)
PORTL.0: P12.2, SHIELD1.41 (PG0)
PORTL.1: P12.3, SHIELD1.40 (PG1)
PORTL.2: P12.4, SHIELD1.39 (PG2)
PORTL.3: P12.5, SHIELD1.38 (PD7)

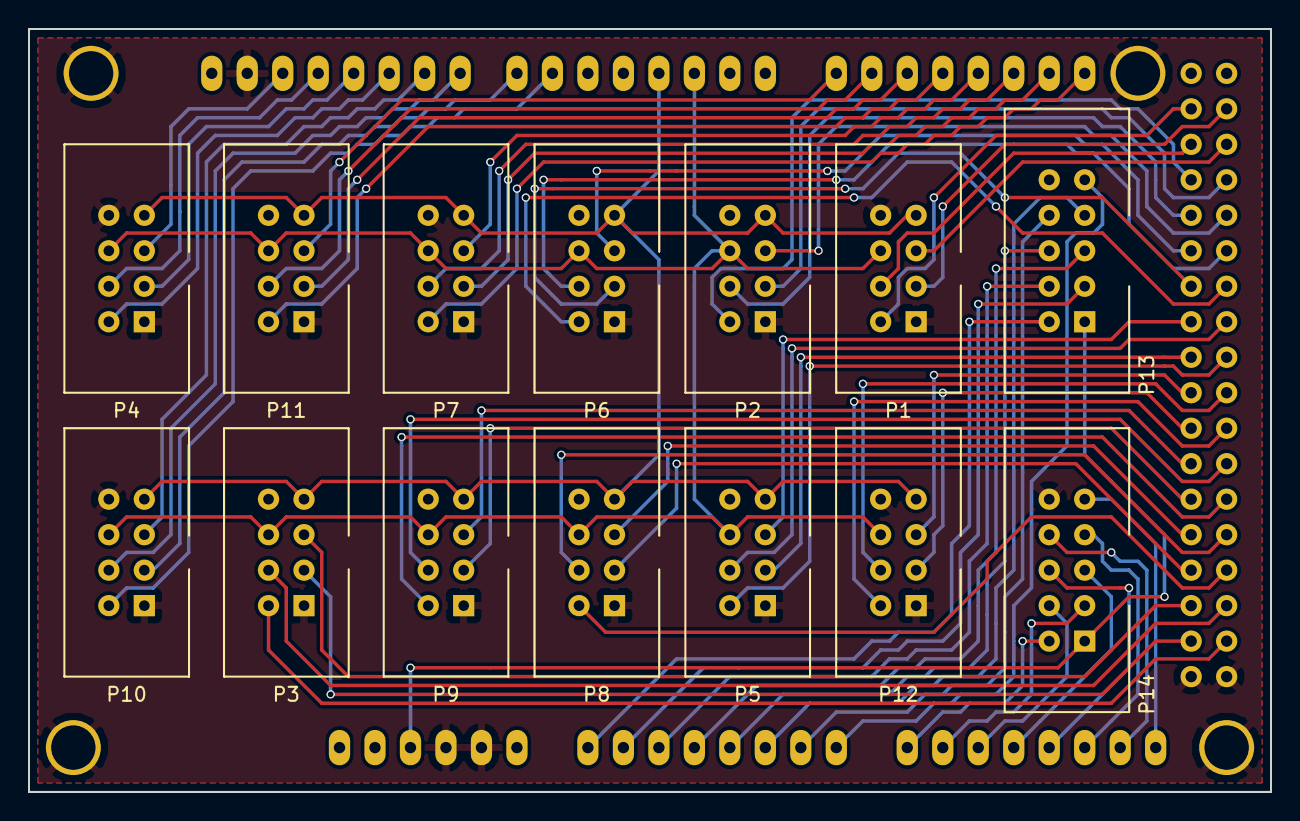
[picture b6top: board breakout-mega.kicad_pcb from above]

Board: 2 copper layers, 88.9 x 54.6 mm, 15 parts (0 on the bottom side), 68 nets.

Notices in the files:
kicad/a320/ecam-panel/ecam-panel.kicad_pcb:
Copyright (C) 2017 Alvaro Polo
kicad/breakout-mega/breakout-mega.kicad_pcb:
Copyright (C) 2016-2017 Alvaro Polo
